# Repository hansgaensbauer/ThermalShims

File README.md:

# Thermal Shims

## Shim Demos

### Concentric Rings

This demonstration uses a 4mm ferrite plate cut to size on a waterjet. Each ring is connected to a PCB heater that is counterwound to prevent the development of magnetic fields from the heater current.

### 12x12 Array

This board demonstrates independent closed-loop control over the temperature of 144 ferrite elements. Each ferrite element has a temperature control unit cell attached on the backside of the PCB. This circuit uses two dual-MOSFETs to provide DRAM-like array access to the power setting and temperature readout for that element:

These unit cells can then be connected to form a larger array of N elements, with only sqrt(N) control circuits/ADCs required:

The `12x12 Array` folder contains simulations of the control circuits showing the sequencing required to measure the temperature or set the cell power level. All of this circuitry is included on the PCB for the 12x12 array demo.

### Hub & Spoke NdFeB Magnet Shimming

This board provides temperature control and sensing for 32 NdFeB magnets in a hub & spoke magnet array. This can be used to prevent temperature drift between the magnets during a scan, or even to account for variations in the magnetization of the individual elements. 

## Simulations
The jupyter notebook in the Simulations folder includes code for simulating different arrangements of thermal shims with different temperatures using [FEMM](https://www.femm.info/). These simulations assume an arctangent B/H curve that is parameterized by a linear relationship between the saturation magnetization and the temperature:

To run a simulation with a certain material and temperature, the code creates a custom material based on the calculated BH curve in FEMM. To sweep the temperature, the same simulation is run with different materials.

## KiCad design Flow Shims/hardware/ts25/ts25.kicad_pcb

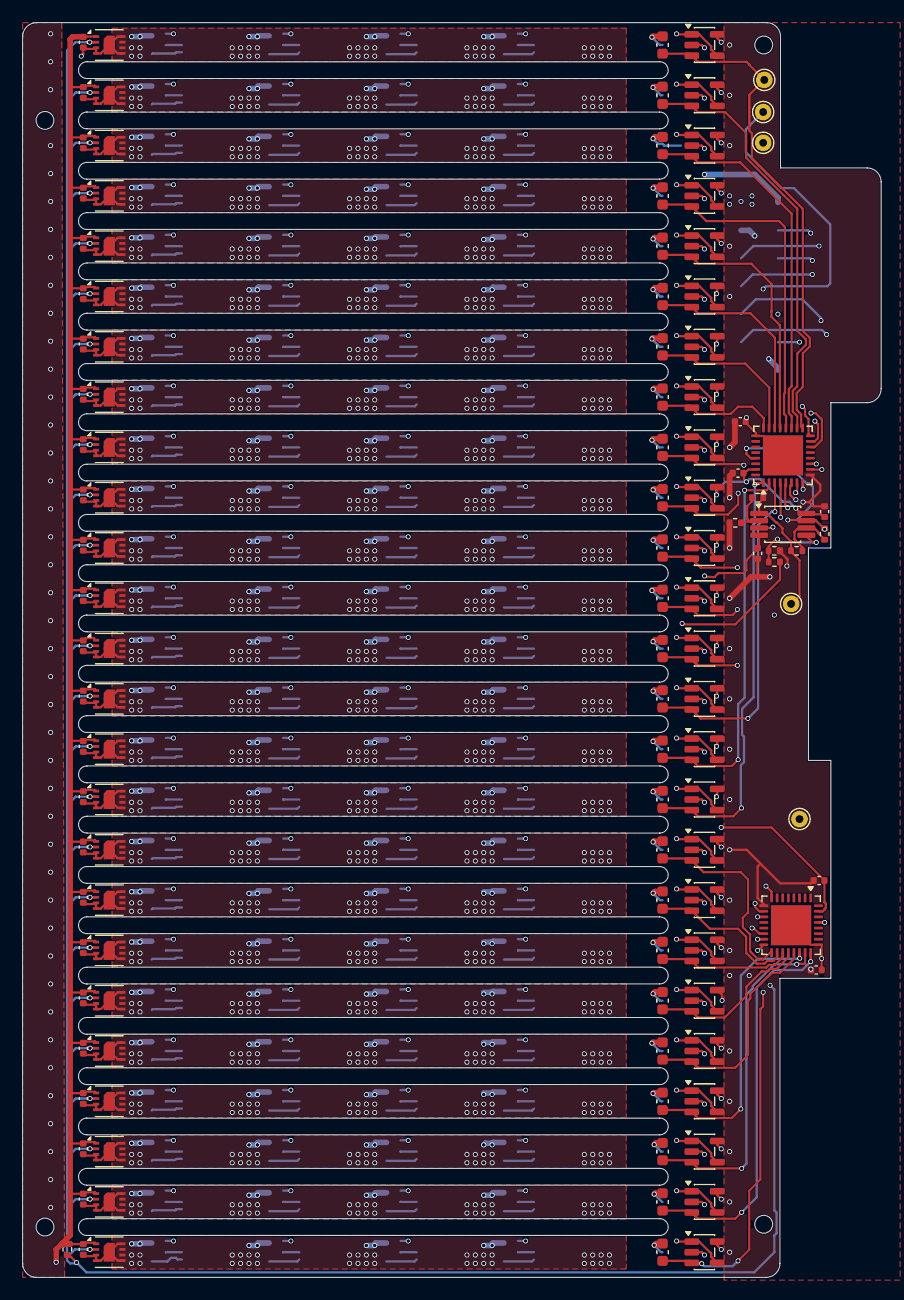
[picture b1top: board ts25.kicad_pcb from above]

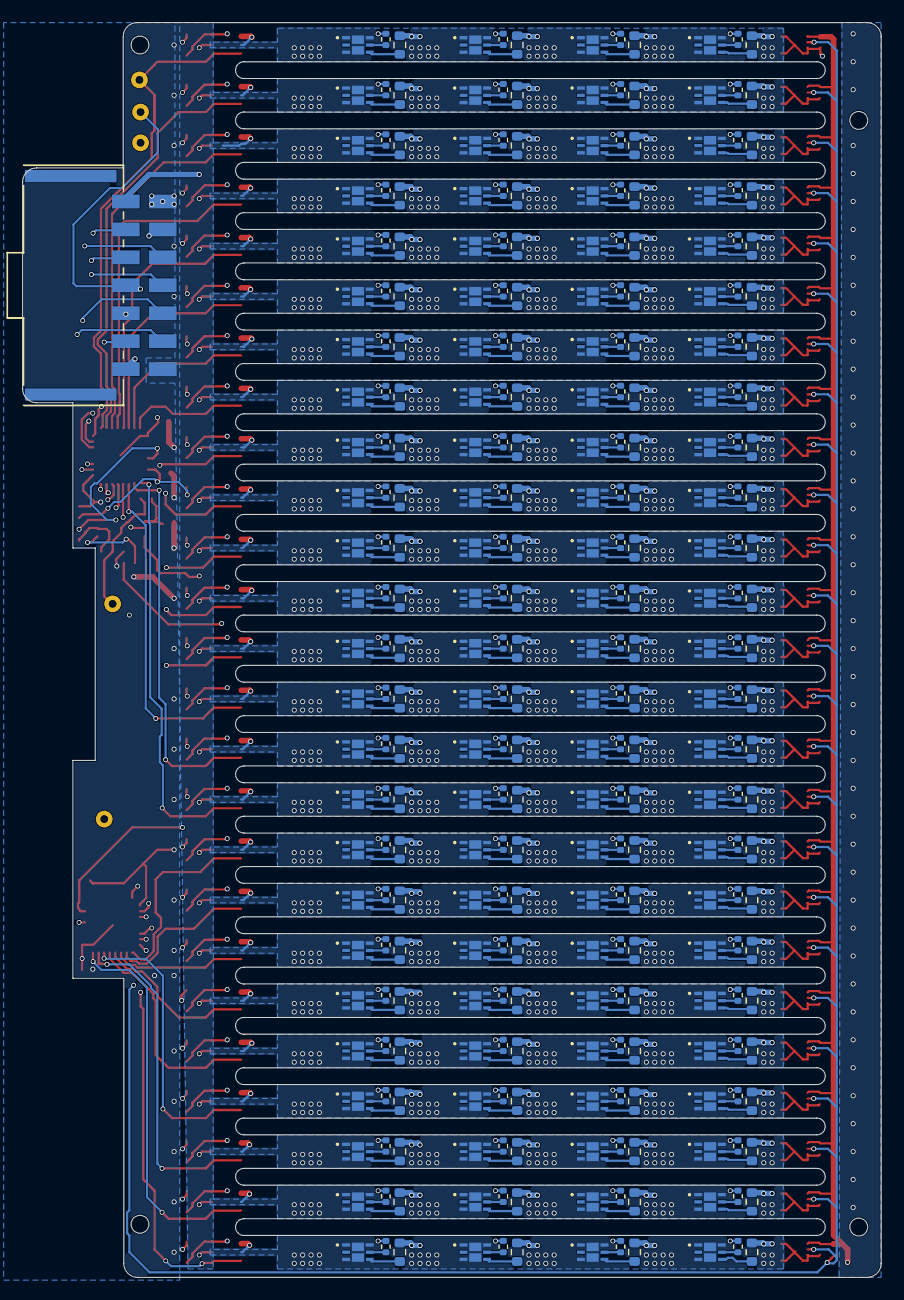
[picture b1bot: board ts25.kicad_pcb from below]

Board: 4 copper layers, 76.8 x 112.2 mm, 422 parts (301 on the bottom side), 269 nets.

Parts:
C1, C2, C3, C4, C5, C6, C7, C8, C9, C10, C11, C12, C13, C14, C15, C16, C17, C18, C19, C20, C21, C22, C23, C24, C25, C26, C27, C28, C29, C56, C57: 100n; C_0402_1005Metric
C30, C31, C32, C33, C34, C35, C36, C37, C38, C39, C40, C41, C42, C43, C44, C45, C46, C47, C48, C49, C50, C51, C52, C53, C54: 100n; C_0603_1608Metric
J2: Nano-Fit; CONN_SD-105405-001_14_MOL
R1: R_Small; R_0402_1005Metric
R2, R3, R4, R5, R6, R7: 10k; R_0402_1005Metric
R8, R9, R10, R11, R12, R13, R14, R15, R16, R17, R18, R19, R20, R21, R22, R23, R24, R25, R26, R27, R28, R29, R30, R31, R32, R59, R61, R63, R65, R67, R69, R71, R73, R75, R77, R79, R81, R83, R85, R87, R89, R91, R93, R95, R97, R99, R101, R103, R105, R107, R109, R111, R113, R115, R117, R119, R121, R123, R125, R127, R129, R131, R133, R135, R137, R139, R141, R143, R145, R147, R149, R151, R153, R155, R157, R159, R161, R163, R165, R167, R169, R171, R173, R175, R177, R179, R181, R183, R185, R187, R189, R191, R193, R195, R197, R199, R201, R203, R205, R207: 5; R_0603_1608Metric
R33, R34, R35, R36, R37, R38, R39, R40, R41, R42, R43, R44, R45, R46, R47, R48, R49, R50, R51, R52, R53, R54, R55, R56, R57, R58, R60, R62, R64, R66, R68, R70, R72, R74, R76, R78, R80, R82, R84, R86, R88, R90, R92, R94, R96, R98, R100, R102, R104, R106, R108, R110, R112, R114, R116, R118, R120, R122, R124, R126, R128, R130, R132, R134, R136, R138, R140, R142, R144, R146, R148, R150, R152, R154, R156, R158, R160, R162, R164, R166, R168, R170, R172, R174, R176, R178, R180, R182, R184, R186, R188, R190, R192, R194, R196, R198, R200, R202, R204, R206: 10; R_0402_1005Metric
TP1, TP2, TP3, TP4, TP5: TestPoint; TestPoint_THTPad_D1.5mm_Drill0.7mm
U1, U27: ADG5206; QFN-32-1EP_5x5mm_P0.5mm_EP3.6x3.6mm
U2, U3, U4, U5, U6, U7, U8, U9, U10, U11, U12, U13, U14, U15, U16, U17, U18, U19, U20, U21, U22, U23, U24, U25, U26: TMP1826NG; Sensirion_DFN-8-1EP_2.5x2.5mm_P0.5mm_EP1.1x1.7mm
U28: OPA2196xDGK; VSSOP-8_3x3mm_P0.65mm
U29, U30, U31, U32, U33, U34, U35, U36, U37, U38, U39, U40, U41, U42, U43, U44, U45, U46, U47, U48, U49, U50, U51, U52, U78, U79, U80, U81, U82, U83, U84, U85, U86, U87, U88, U89, U90, U91, U92, U93, U94, U95, U96, U97, U98, U99, U100, U101, U102, U103, U104, U105, U106, U107, U108, U109, U110, U111, U112, U113, U114, U115, U116, U117, U118, U119, U120, U121, U122, U123, U124, U125, U126, U127, U128, U129, U130, U131, U132, U133, U134, U135, U136, U137, U138, U139, U140, U141, U142, U143, U144, U145, U146, U147, U148, U149, U150, U151, U152, U153: WDFN6_2x2_ONS-M
U53, U54, U55, U56, U57, U58, U59, U60, U61, U62, U63, U64, U65, U66, U67, U68, U69, U70, U71, U72, U73, U74, U75, U76, U77: OPA196xDBV; SOT-23-5

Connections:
+3.3V: C1.2, C2.2, C3.2, C4.2, C5.2, C6.2, C7.2, C8.2, C9.2, C10.2, C11.2, C12.2, C13.2, C14.2, C15.2, C16.2, C17.2, C18.2, C19.2, C20.2, C21.2, C22.2, C23.2, C24.2, C25.2, J2.6, R1.2, U2.1 (V+), U3.1 (V+), U4.1 (V+), U5.1 (V+), U6.1 (V+), U7.1 (V+), U8.1 (V+), U9.1 (V+), U10.1 (V+), U11.1 (V+), U12.1 (V+), U13.1 (V+), U14.1 (V+), U15.1 (V+), U16.1 (V+), U17.1 (V+), U18.1 (V+), U19.1 (V+), U20.1 (V+), U21.1 (V+), U22.1 (V+), U23.1 (V+), U24.1 (V+), U25.1 (V+), U26.1 (V+)
+15V: C28.2, C29.2, C56.1, J2.8, U1.31 (VDD), U27.31 (VDD), U28.8 (V+), U53.5 (V+), U54.5 (V+), U55.5 (V+), U56.5 (V+), U57.5 (V+), U58.5 (V+), U59.5 (V+), U60.5 (V+), U61.5 (V+), U62.5 (V+), U63.5 (V+), U64.5 (V+), U65.5 (V+), U66.5 (V+), U67.5 (V+), U68.5 (V+), U69.5 (V+), U70.5 (V+), U71.5 (V+), U72.5 (V+), U73.5 (V+), U74.5 (V+), U75.5 (V+), U76.5 (V+), U77.5 (V+)
-15V: C26.2, C27.2, C57.1, J2.14, U1.25 (VSS), U1.33 (PAD), U27.25 (VSS), U27.33 (PAD), U28.4 (V-), U53.2 (V-), U54.2 (V-), U55.2 (V-), U56.2 (V-), U57.2 (V-), U58.2 (V-), U59.2 (V-), U60.2 (V-), U61.2 (V-), U62.2 (V-), U63.2 (V-), U64.2 (V-), U65.2 (V-), U66.2 (V-), U67.2 (V-), U68.2 (V-), U69.2 (V-), U70.2 (V-), U71.2 (V-), U72.2 (V-), U73.2 (V-), U74.2 (V-), U75.2 (V-), U76.2 (V-), U77.2 (V-)
/A0: J2.5, U1.15 (A0), U27.15 (A0)
/A1: J2.4, U1.14 (A1), U27.14 (A1)
/A2: J2.3, U1.11 (A2), U27.11 (A2)
/A3: J2.2, U1.10 (A3), U27.10 (A3)
/EN0: J2.12, U1.16 (EN)
/EN1: J2.13, U27.16 (EN)
/VG: R7.1, TP4.1 (1_1), U1.29 (D), U27.29 (D), U28.7
/VG1: C30.1, TP5.1 (1_1), U1.17 (S1), U53.3 (+)
/VG2: C31.1, U1.18 (S2), U54.3 (+)
/VG3: C32.1, U1.19 (S3), U55.3 (+)
/VG4: C33.1, U1.20 (S4), U56.3 (+)
/VG5: C34.1, U1.21 (S5), U57.3 (+)
/VG6: C35.1, U1.22 (S6), U58.3 (+)
/VG7: C36.1, U1.23 (S7), U59.3 (+)
/VG8: C37.1, U1.24 (S8), U60.3 (+)
/VG9: C38.1, U1.8 (S9), U61.3 (+)
/VG10: C39.1, U1.7 (S10), U62.3 (+)
/VG11: C40.1, U1.6 (S11), U63.3 (+)
/VG12: C41.1, U1.5 (S12), U64.3 (+)
/VG13: C42.1, U1.4 (S13), U65.3 (+)
/VG14: C43.1, U1.3 (S14), U66.3 (+)
/VG15: C44.1, U1.2 (S15), U67.3 (+)
/VG16: C45.1, U1.1 (S16), U68.3 (+)
/VG17: C46.1, U27.17 (S1), U69.3 (+)
/VG18: C47.1, U27.18 (S2), U70.3 (+)
/VG19: C48.1, U27.19 (S3), U71.3 (+)
/VG20: C49.1, U27.20 (S4), U72.3 (+)
/VG21: C50.1, U27.21 (S5), U73.3 (+)
/VG22: C51.1, U27.22 (S6), U74.3 (+)
/VG23: C52.1, U27.23 (S7), U75.3 (+)
/VG24: C53.1, U27.24 (S8), U76.3 (+)
/VG25: C54.1, U27.8 (S9), U77.3 (+)
/VGIN: J2.11, TP2.1 (1_1), U28.3 (+)
/VTEMP: J2.10, R1.1, U2.2 (SDQ), U3.2 (SDQ), U4.2 (SDQ), U5.2 (SDQ), U6.2 (SDQ), U7.2 (SDQ), U8.2 (SDQ), U9.2 (SDQ), U10.2 (SDQ), U11.2 (SDQ), U12.2 (SDQ), U13.2 (SDQ), U14.2 (SDQ), U15.2 (SDQ), U16.2 (SDQ), U17.2 (SDQ), U18.2 (SDQ), U19.2 (SDQ), U20.2 (SDQ), U21.2 (SDQ), U22.2 (SDQ), U23.2 (SDQ), U24.2 (SDQ), U25.2 (SDQ), U26.2 (SDQ)
GND: C1.1, C2.1, C3.1, C4.1, C5.1, C6.1, C7.1, C8.1, C9.1, C10.1, C11.1, C12.1, C13.1, C14.1, C15.1, C16.1, C17.1, C18.1, C19.1, C20.1, C21.1, C22.1, C23.1, C24.1, C25.1, C26.1, C27.1, C28.1, C29.1, C30.2, C31.2, C32.2, C33.2, C34.2, C35.2, C36.2, C37.2, C38.2, C39.2, C40.2, C41.2, C42.2, C43.2, C44.2, C45.2, C46.2, C47.2, C48.2, C49.2, C50.2, C51.2, C52.2, C53.2, C54.2, C56.2, C57.2, J2.1, R3.1, R4.1, U1.9 (GND), U2.3 (ADDR), U2.4 (GND), U2.5 (IO3), U2.6 (IO0), U2.7 (IO1), U2.8 (~ALERT), U2.9 (PAD), U3.3 (ADDR), U3.4 (GND), U3.5 (IO3), U3.6 (IO0), U3.7 (IO1), U3.8 (~ALERT), U3.9 (PAD), U4.3 (ADDR), U4.4 (GND), U4.5 (IO3), U4.6 (IO0), U4.7 (IO1), U4.8 (~ALERT), U4.9 (PAD), U5.3 (ADDR), U5.4 (GND), U5.5 (IO3), U5.6 (IO0), U5.7 (IO1), U5.8 (~ALERT), U5.9 (PAD), U6.3 (ADDR), U6.4 (GND), U6.5 (IO3), U6.6 (IO0), U6.7 (IO1), U6.8 (~ALERT), U6.9 (PAD), U7.3 (ADDR), U7.4 (GND), U7.5 (IO3), U7.6 (IO0), U7.7 (IO1), U7.8 (~ALERT), U7.9 (PAD), U8.3 (ADDR), U8.4 (GND), U8.5 (IO3), U8.6 (IO0), U8.7 (IO1), U8.8 (~ALERT), U8.9 (PAD), U9.3 (ADDR), U9.4 (GND), U9.5 (IO3), U9.6 (IO0), U9.7 (IO1), U9.8 (~ALERT), U9.9 (PAD), U10.3 (ADDR), U10.4 (GND), U10.5 (IO3), U10.6 (IO0), U10.7 (IO1), U10.8 (~ALERT), U10.9 (PAD), U11.3 (ADDR), U11.4 (GND), U11.5 (IO3), U11.6 (IO0), U11.7 (IO1), U11.8 (~ALERT), U11.9 (PAD), U12.3 (ADDR), U12.4 (GND), U12.5 (IO3), U12.6 (IO0), U12.7 (IO1), U12.8 (~ALERT), U12.9 (PAD), U13.3 (ADDR), U13.4 (GND), U13.5 (IO3), U13.6 (IO0), U13.7 (IO1), U13.8 (~ALERT), U13.9 (PAD), U14.3 (ADDR), U14.4 (GND), U14.5 (IO3), U14.6 (IO0), U14.7 (IO1), U14.8 (~ALERT), U14.9 (PAD), U15.3 (ADDR), U15.4 (GND), U15.5 (IO3), U15.6 (IO0), U15.7 (IO1), U15.8 (~ALERT), U15.9 (PAD), U16.3 (ADDR), U16.4 (GND), U16.5 (IO3), U16.6 (IO0), U16.7 (IO1), U16.8 (~ALERT), U16.9 (PAD), U17.3 (ADDR), U17.4 (GND), U17.5 (IO3), U17.6 (IO0), U17.7 (IO1), U17.8 (~ALERT), U17.9 (PAD), U18.3 (ADDR), U18.4 (GND), U18.5 (IO3), U18.6 (IO0), U18.7 (IO1), U18.8 (~ALERT), U18.9 (PAD), U19.3 (ADDR), U19.4 (GND), U19.5 (IO3), U19.6 (IO0), U19.7 (IO1), U19.8 (~ALERT), U19.9 (PAD), U20.3 (ADDR), U20.4 (GND), U20.5 (IO3), U20.6 (IO0), U20.7 (IO1), U20.8 (~ALERT), U20.9 (PAD), U21.3 (ADDR), U21.4 (GND), U21.5 (IO3), U21.6 (IO0), U21.7 (IO1), U21.8 (~ALERT), U21.9 (PAD), U22.3 (ADDR), U22.4 (GND), U22.5 (IO3), U22.6 (IO0), U22.7 (IO1), U22.8 (~ALERT), U22.9 (PAD), U23.3 (ADDR), U23.4 (GND), U23.5 (IO3), U23.6 (IO0), U23.7 (IO1), U23.8 (~ALERT), U23.9 (PAD), U24.3 (ADDR), U24.4 (GND), U24.5 (IO3), U24.6 (IO0), U24.7 (IO1), U24.8 (~ALERT), U24.9 (PAD), U25.3 (ADDR), U25.4 (GND), U25.5 (IO3), U25.6 (IO0), U25.7 (IO1), U25.8 (~ALERT), U25.9 (PAD), U26.3 (ADDR), U26.4 (GND), U26.5 (IO3), U26.6 (IO0), U26.7 (IO1), U26.8 (~ALERT), U26.9 (PAD), U27.9 (GND), U29.1 (A), U29.3 (D), U29.6 (K), U29.7 (K), U29.8 (D), U30.1 (A), U30.3 (D), U30.6 (K), U30.7 (K), U30.8 (D), U31.1 (A), U31.3 (D), U31.6 (K), U31.7 (K), U31.8 (D), U32.1 (A), U32.3 (D), U32.6 (K), U32.7 (K), U32.8 (D), U33.1 (A), U33.3 (D), U33.6 (K), U33.7 (K), U33.8 (D), U34.1 (A), U34.3 (D), U34.6 (K), U34.7 (K), U34.8 (D), U35.1 (A), U35.3 (D), U35.6 (K), U35.7 (K), U35.8 (D), U36.1 (A), U36.3 (D), U36.6 (K), U36.7 (K), U36.8 (D), U37.1 (A), U37.3 (D), U37.6 (K), U37.7 (K), U37.8 (D), U38.1 (A), U38.3 (D), U38.6 (K), U38.7 (K), U38.8 (D), U39.1 (A), U39.3 (D), U39.6 (K), U39.7 (K), U39.8 (D), U40.1 (A), U40.3 (D), U40.6 (K), U40.7 (K), U40.8 (D), U41.1 (A), U41.3 (D), U41.6 (K), U41.7 (K), U41.8 (D), U42.1 (A), U42.3 (D), U42.6 (K), U42.7 (K), U42.8 (D), U43.1 (A), U43.3 (D), U43.6 (K), U43.7 (K), U43.8 (D), U44.1 (A), U44.3 (D), U44.6 (K), U44.7 (K), U44.8 (D), U45.1 (A), U45.3 (D), U45.6 (K), U45.7 (K), U45.8 (D), U46.1 (A), U46.3 (D), U46.6 (K), U46.7 (K), U46.8 (D), U47.1 (A), U47.3 (D), U47.6 (K), U47.7 (K), U47.8 (D), U48.1 (A), U48.3 (D), U48.6 (K), U48.7 (K), U48.8 (D), U49.1 (A), U49.3 (D), U49.6 (K), U49.7 (K), U49.8 (D), U50.1 (A), U50.3 (D), U50.6 (K), U50.7 (K), U50.8 (D), U51.1 (A), U51.3 (D), U51.6 (K), U51.7 (K), U51.8 (D), U52.1 (A), U52.3 (D), U52.6 (K), U52.7 (K), U52.8 (D), U78.1 (A), U78.3 (D), U78.6 (K), U78.7 (K), U78.8 (D), U79.1 (A), U79.3 (D), U79.6 (K), U79.7 (K), U79.8 (D), U80.1 (A), U80.3 (D), U80.6 (K), U80.7 (K), U80.8 (D), U81.1 (A), U81.3 (D), U81.6 (K), U81.7 (K), U81.8 (D), U82.1 (A), U82.3 (D), U82.6 (K), U82.7 (K), U82.8 (D), U83.1 (A), U83.3 (D), U83.6 (K), U83.7 (K), U83.8 (D), U84.1 (A), U84.3 (D), U84.6 (K), U84.7 (K), U84.8 (D), U85.1 (A), U85.3 (D), U85.6 (K), U85.7 (K), U85.8 (D), U86.1 (A), U86.3 (D), U86.6 (K), U86.7 (K), U86.8 (D), U87.1 (A), U87.3 (D), U87.6 (K), U87.7 (K), U87.8 (D), U88.1 (A), U88.3 (D), U88.6 (K), U88.7 (K), U88.8 (D), U89.1 (A), U89.3 (D), U89.6 (K), U89.7 (K), U89.8 (D), U90.1 (A), U90.3 (D), U90.6 (K), U90.7 (K), U90.8 (D), U91.1 (A), U91.3 (D), U91.6 (K), U91.7 (K), U91.8 (D), U92.1 (A), U92.3 (D), U92.6 (K), U92.7 (K), U92.8 (D), U93.1 (A), U93.3 (D), U93.6 (K), U93.7 (K), U93.8 (D), U94.1 (A), U94.3 (D), U94.6 (K), U94.7 (K), U94.8 (D), U95.1 (A), U95.3 (D), U95.6 (K), U95.7 (K), U95.8 (D), U96.1 (A), U96.3 (D), U96.6 (K), U96.7 (K), U96.8 (D), U97.1 (A), U97.3 (D), U97.6 (K), U97.7 (K), U97.8 (D), U98.1 (A), U98.3 (D), U98.6 (K), U98.7 (K), U98.8 (D), U99.1 (A), U99.3 (D), U99.6 (K), U99.7 (K), U99.8 (D), U100.1 (A), U100.3 (D), U100.6 (K), U100.7 (K), U100.8 (D), U101.1 (A), U101.3 (D), U101.6 (K), U101.7 (K), U101.8 (D), U102.1 (A), U102.3 (D), U102.6 (K), U102.7 (K), U102.8 (D), U103.1 (A), U103.3 (D), U103.6 (K), U103.7 (K), U103.8 (D), U104.1 (A), U104.3 (D), U104.6 (K), U104.7 (K), U104.8 (D), U105.1 (A), U105.3 (D), U105.6 (K), U105.7 (K), U105.8 (D), U106.1 (A), U106.3 (D), U106.6 (K), U106.7 (K), U106.8 (D), U107.1 (A), U107.3 (D), U107.6 (K), U107.7 (K), U107.8 (D), U108.1 (A), U108.3 (D), U108.6 (K), U108.7 (K), U108.8 (D), U109.1 (A), U109.3 (D), U109.6 (K), U109.7 (K), U109.8 (D), U110.1 (A), U110.3 (D), U110.6 (K), U110.7 (K), U110.8 (D), U111.1 (A), U111.3 (D), U111.6 (K), U111.7 (K), U111.8 (D), U112.1 (A), U112.3 (D), U112.6 (K), U112.7 (K), U112.8 (D), U113.1 (A), U113.3 (D), U113.6 (K), U113.7 (K), U113.8 (D), U114.1 (A), U114.3 (D), U114.6 (K), U114.7 (K), U114.8 (D), U115.1 (A), U115.3 (D), U115.6 (K), U115.7 (K), U115.8 (D), U116.1 (A), U116.3 (D), U116.6 (K), U116.7 (K), U116.8 (D), U117.1 (A), U117.3 (D), U117.6 (K), U117.7 (K), U117.8 (D), U118.1 (A), U118.3 (D), U118.6 (K)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
unnamed: J2.9, TP1.1 (1_1)
unnamed: R2.2, R6.1, TP3.1 (1_1), U28.1
unnamed: R2.1, R3.2, U28.2 (-)
unnamed: R4.2, R5.1, U28.5 (+)
unnamed: R6.2, R7.2, U28.6 (-)
unnamed: R33.1, U29.5 (G)
unnamed: R8.2, U29.4 (S)
unnamed: R34.1, U30.5 (G)
unnamed: R9.2, U30.4 (S)
unnamed: R35.1, U31.5 (G)
unnamed: R10.2, U31.4 (S)
unnamed: R36.1, U32.5 (G)
unnamed: R11.2, U32.4 (S)
unnamed: R37.1, U33.5 (G)
unnamed: R12.2, U33.4 (S)
unnamed: R38.1, U34.5 (G)
unnamed: R13.2, U34.4 (S)
unnamed: R39.1, U35.5 (G)
unnamed: R14.2, U35.4 (S)
unnamed: R40.1, U36.5 (G)
unnamed: R15.2, U36.4 (S)
unnamed: R41.1, U37.5 (G)
unnamed: R16.2, U37.4 (S)
unnamed: R42.1, U38.5 (G)
unnamed: R17.2, U38.4 (S)
unnamed: R43.1, U39.5 (G)
unnamed: R18.2, U39.4 (S)
unnamed: R44.1, U40.5 (G)
unnamed: R19.2, U40.4 (S)
unnamed: R45.1, U41.5 (G)
unnamed: R20.2, U41.4 (S)
unnamed: R46.1, U42.5 (G)
unnamed: R21.2, U42.4 (S)
unnamed: R47.1, U43.5 (G)
unnamed: R22.2, U43.4 (S)
unnamed: R48.1, U44.5 (G)
unnamed: R23.2, U44.4 (S)
unnamed: R49.1, U45.5 (G)
unnamed: R24.2, U45.4 (S)
unnamed: R50.1, U46.5 (G)
unnamed: R25.2, U46.4 (S)
unnamed: R51.1, U47.5 (G)
unnamed: R26.2, U47.4 (S)
unnamed: R52.1, U48.5 (G)
unnamed: R27.2, U48.4 (S)
unnamed: R53.1, U49.5 (G)
unnamed: R28.2, U49.4 (S)
unnamed: R54.1, U50.5 (G)
unnamed: R29.2, U50.4 (S)
unnamed: R55.1, U51.5 (G)
unnamed: R30.2, U51.4 (S)
unnamed: R56.1, U52.5 (G)
unnamed: R31.2, U52.4 (S)
unnamed: R33.2, R58.2, R108.2, R158.2, U53.1, U53.4 (-)
unnamed: R34.2, R60.2, R110.2, R160.2, U54.1, U54.4 (-)
unnamed: R35.2, R62.2, R112.2, R162.2, U55.1, U55.4 (-)
unnamed: R36.2, R64.2, R114.2, R164.2, U56.1, U56.4 (-)
unnamed: R37.2, R66.2, R116.2, R166.2, U57.1, U57.4 (-)
unnamed: R38.2, R68.2, R118.2, R168.2, U58.1, U58.4 (-)
unnamed: R39.2, R70.2, R120.2, R170.2, U59.1, U59.4 (-)
unnamed: R40.2, R72.2, R122.2, R172.2, U60.1, U60.4 (-)
unnamed: R41.2, R74.2, R124.2, R174.2, U61.1, U61.4 (-)
unnamed: R42.2, R76.2, R126.2, R176.2, U62.1, U62.4 (-)
unnamed: R43.2, R78.2, R128.2, R178.2, U63.1, U63.4 (-)
unnamed: R44.2, R80.2, R130.2, R180.2, U64.1, U64.4 (-)
unnamed: R45.2, R82.2, R132.2, R182.2, U65.1, U65.4 (-)
unnamed: R46.2, R84.2, R134.2, R184.2, U66.1, U66.4 (-)
unnamed: R47.2, R86.2, R136.2, R186.2, U67.1, U67.4 (-)
unnamed: R48.2, R88.2, R138.2, R188.2, U68.1, U68.4 (-)
unnamed: R49.2, R90.2, R140.2, R190.2, U69.1, U69.4 (-)
unnamed: R50.2, R92.2, R142.2, R192.2, U70.1, U70.4 (-)
unnamed: R51.2, R94.2, R144.2, R194.2, U71.1, U71.4 (-)
unnamed: R52.2, R96.2, R146.2, R196.2, U72.1, U72.4 (-)
unnamed: R53.2, R98.2, R148.2, R198.2, U73.1, U73.4 (-)
unnamed: R54.2, R100.2, R150.2, R200.2, U74.1, U74.4 (-)
unnamed: R55.2, R102.2, R152.2, R202.2, U75.1, U75.4 (-)
unnamed: R56.2, R104.2, R154.2, R204.2, U76.1, U76.4 (-)
unnamed: R57.2, R106.2, R156.2, R206.2, U77.1, U77.4 (-)
unnamed: R57.1, U78.5 (G)
unnamed: R32.2, U78.4 (S)
unnamed: R58.1, U79.5 (G)
unnamed: R59.2, U79.4 (S)
unnamed: R60.1, U80.5 (G)
unnamed: R61.2, U80.4 (S)
unnamed: R62.1, U81.5 (G)
unnamed: R63.2, U81.4 (S)
unnamed: R64.1, U82.5 (G)
unnamed: R65.2, U82.4 (S)
unnamed: R66.1, U83.5 (G)
unnamed: R67.2, U83.4 (S)
unnamed: R68.1, U84.5 (G)
unnamed: R69.2, U84.4 (S)
unnamed: R70.1, U85.5 (G)
unnamed: R71.2, U85.4 (S)
unnamed: R72.1, U86.5 (G)
unnamed: R73.2, U86.4 (S)
unnamed: R74.1, U87.5 (G)
unnamed: R75.2, U87.4 (S)
unnamed: R76.1, U88.5 (G)
unnamed: R77.2, U88.4 (S)
unnamed: R78.1, U89.5 (G)
unnamed: R79.2, U89.4 (S)
unnamed: R80.1, U90.5 (G)
unnamed: R81.2, U90.4 (S)
unnamed: R82.1, U91.5 (G)
unnamed: R83.2, U91.4 (S)
unnamed: R84.1, U92.5 (G)
unnamed: R85.2, U92.4 (S)
unnamed: R86.1, U93.5 (G)
unnamed: R87.2, U93.4 (S)
unnamed: R88.1, U94.5 (G)
unnamed: R89.2, U94.4 (S)
unnamed: R90.1, U95.5 (G)
unnamed: R91.2, U95.4 (S)
unnamed: R92.1, U96.5 (G)
unnamed: R93.2, U96.4 (S)
unnamed: R94.1, U97.5 (G)
unnamed: R95.2, U97.4 (S)
unnamed: R96.1, U98.5 (G)
unnamed: R97.2, U98.4 (S)
unnamed: R98.1, U99.5 (G)
unnamed: R99.2, U99.4 (S)
unnamed: R100.1, U100.5 (G)
unnamed: R101.2, U100.4 (S)
unnamed: R102.1, U101.5 (G)
unnamed: R103.2, U101.4 (S)
unnamed: R104.1, U102.5 (G)
unnamed: R105.2, U102.4 (S)
unnamed: R106.1, U103.5 (G)
unnamed: R107.2, U103.4 (S)
unnamed: R108.1, U104.5 (G)
unnamed: R109.2, U104.4 (S)
unnamed: R110.1, U105.5 (G)
unnamed: R111.2, U105.4 (S)
unnamed: R112.1, U106.5 (G)
unnamed: R113.2, U106.4 (S)
unnamed: R114.1, U107.5 (G)
unnamed: R115.2, U107.4 (S)
unnamed: R116.1, U108.5 (G)
unnamed: R117.2, U108.4 (S)
unnamed: R118.1, U109.5 (G)
unnamed: R119.2, U109.4 (S)
unnamed: R120.1, U110.5 (G)
unnamed: R121.2, U110.4 (S)
unnamed: R122.1, U111.5 (G)
unnamed: R123.2, U111.4 (S)
unnamed: R124.1, U112.5 (G)
unnamed: R125.2, U112.4 (S)
unnamed: R126.1, U113.5 (G)
unnamed: R127.2, U113.4 (S)
unnamed: R128.1, U114.5 (G)
unnamed: R129.2, U114.4 (S)
unnamed: R130.1, U115.5 (G)
unnamed: R131.2, U115.4 (S)
unnamed: R132.1, U116.5 (G)
unnamed: R133.2, U116.4 (S)
unnamed: R134.1, U117.5 (G)
unnamed: R135.2, U117.4 (S)
unnamed: R136.1, U118.5 (G)
unnamed: R137.2, U118.4 (S)
unnamed: R138.1, U119.5 (G)
unnamed: R139.2, U119.4 (S)
unnamed: R140.1, U120.5 (G)
unnamed: R141.2, U120.4 (S)
unnamed: R142.1, U121.5 (G)
unnamed: R143.2, U121.4 (S)
unnamed: R144.1, U122.5 (G)
unnamed: R145.2, U122.4 (S)
unnamed: R146.1, U123.5 (G)
unnamed: R147.2, U123.4 (S)
unnamed: R148.1, U124.5 (G)
unnamed: R149.2, U124.4 (S)
unnamed: R150.1, U125.5 (G)
unnamed: R151.2, U125.4 (S)
unnamed: R152.1, U126.5 (G)
unnamed: R153.2, U126.4 (S)
unnamed: R154.1, U127.5 (G)
unnamed: R155.2, U127.4 (S)
unnamed: R156.1, U128.5 (G)
unnamed: R157.2, U128.4 (S)
unnamed: R158.1, U129.5 (G)
unnamed: R159.2, U129.4 (S)
unnamed: R160.1, U130.5 (G)
unnamed: R161.2, U130.4 (S)
unnamed: R162.1, U131.5 (G)
unnamed: R163.2, U131.4 (S)
unnamed: R164.1, U132.5 (G)
unnamed: R165.2, U132.4 (S)
unnamed: R166.1, U133.5 (G)
unnamed: R167.2, U133.4 (S)
unnamed: R168.1, U134.5 (G)
unnamed: R169.2, U134.4 (S)
unnamed: R170.1, U135.5 (G)
unnamed: R171.2, U135.4 (S)
unnamed: R172.1, U136.5 (G)
unnamed: R173.2, U136.4 (S)
unnamed: R174.1, U137.5 (G)
unnamed: R175.2, U137.4 (S)
unnamed: R176.1, U138.5 (G)
unnamed: R177.2, U138.4 (S)
unnamed: R178.1, U139.5 (G)
unnamed: R179.2, U139.4 (S)
unnamed: R180.1, U140.5 (G)
unnamed: R181.2, U140.4 (S)
unnamed: R182.1, U141.5 (G)
unnamed: R183.2, U141.4 (S)
unnamed: R184.1, U142.5 (G)
unnamed: R185.2, U142.4 (S)
unnamed: R186.1, U143.5 (G)
unnamed: R187.2, U143.4 (S)
unnamed: R188.1, U144.5 (G)
unnamed: R189.2, U144.4 (S)
unnamed: R190.1, U145.5 (G)
unnamed: R191.2, U145.4 (S)
unnamed: R192.1, U146.5 (G)
unnamed: R193.2, U146.4 (S)
unnamed: R194.1, U147.5 (G)
unnamed: R195.2, U147.4 (S)
unnamed: R196.1, U148.5 (G)
unnamed: R197.2, U148.4 (S)
unnamed: R198.1, U149.5 (G)
unnamed: R199.2, U149.4 (S)
unnamed: R200.1, U150.5 (G)
unnamed: R201.2, U150.4 (S)
unnamed: R202.1, U151.5 (G)
unnamed: R203.2, U151.4 (S)
unnamed: R204.1, U152.5 (G)
unnamed: R205.2, U152.4 (S)
unnamed: R206.1, U153.5 (G)
unnamed: R207.2, U153.4 (S)
VD: J2.7, R5.2, R8.1, R9.1, R10.1, R11.1, R12.1, R13.1, R14.1, R15.1, R16.1, R17.1, R18.1, R19.1, R20.1, R21.1, R22.1, R23.1, R24.1, R25.1, R26.1, R27.1, R28.1, R29.1, R30.1, R31.1, R32.1, R59.1, R61.1, R63.1, R65.1, R67.1, R69.1, R71.1, R73.1, R75.1, R77.1, R79.1, R81.1, R83.1, R85.1, R87.1, R89.1, R91.1, R93.1, R95.1, R97.1, R99.1, R101.1, R103.1, R105.1, R107.1, R109.1, R111.1, R113.1, R115.1, R117.1, R119.1, R121.1, R123.1, R125.1, R127.1, R129.1, R131.1, R133.1, R135.1, R137.1, R139.1, R141.1, R143.1, R145.1, R147.1, R149.1, R151.1, R153.1, R155.1, R157.1, R159.1, R161.1, R163.1, R165.1, R167.1, R169.1, R171.1, R173.1, R175.1, R177.1, R179.1, R181.1, R183.1, R185.1, R187.1, R189.1, R191.1, R193.1, R195.1, R197.1, R199.1, R201.1, R203.1, R205.1, R207.1

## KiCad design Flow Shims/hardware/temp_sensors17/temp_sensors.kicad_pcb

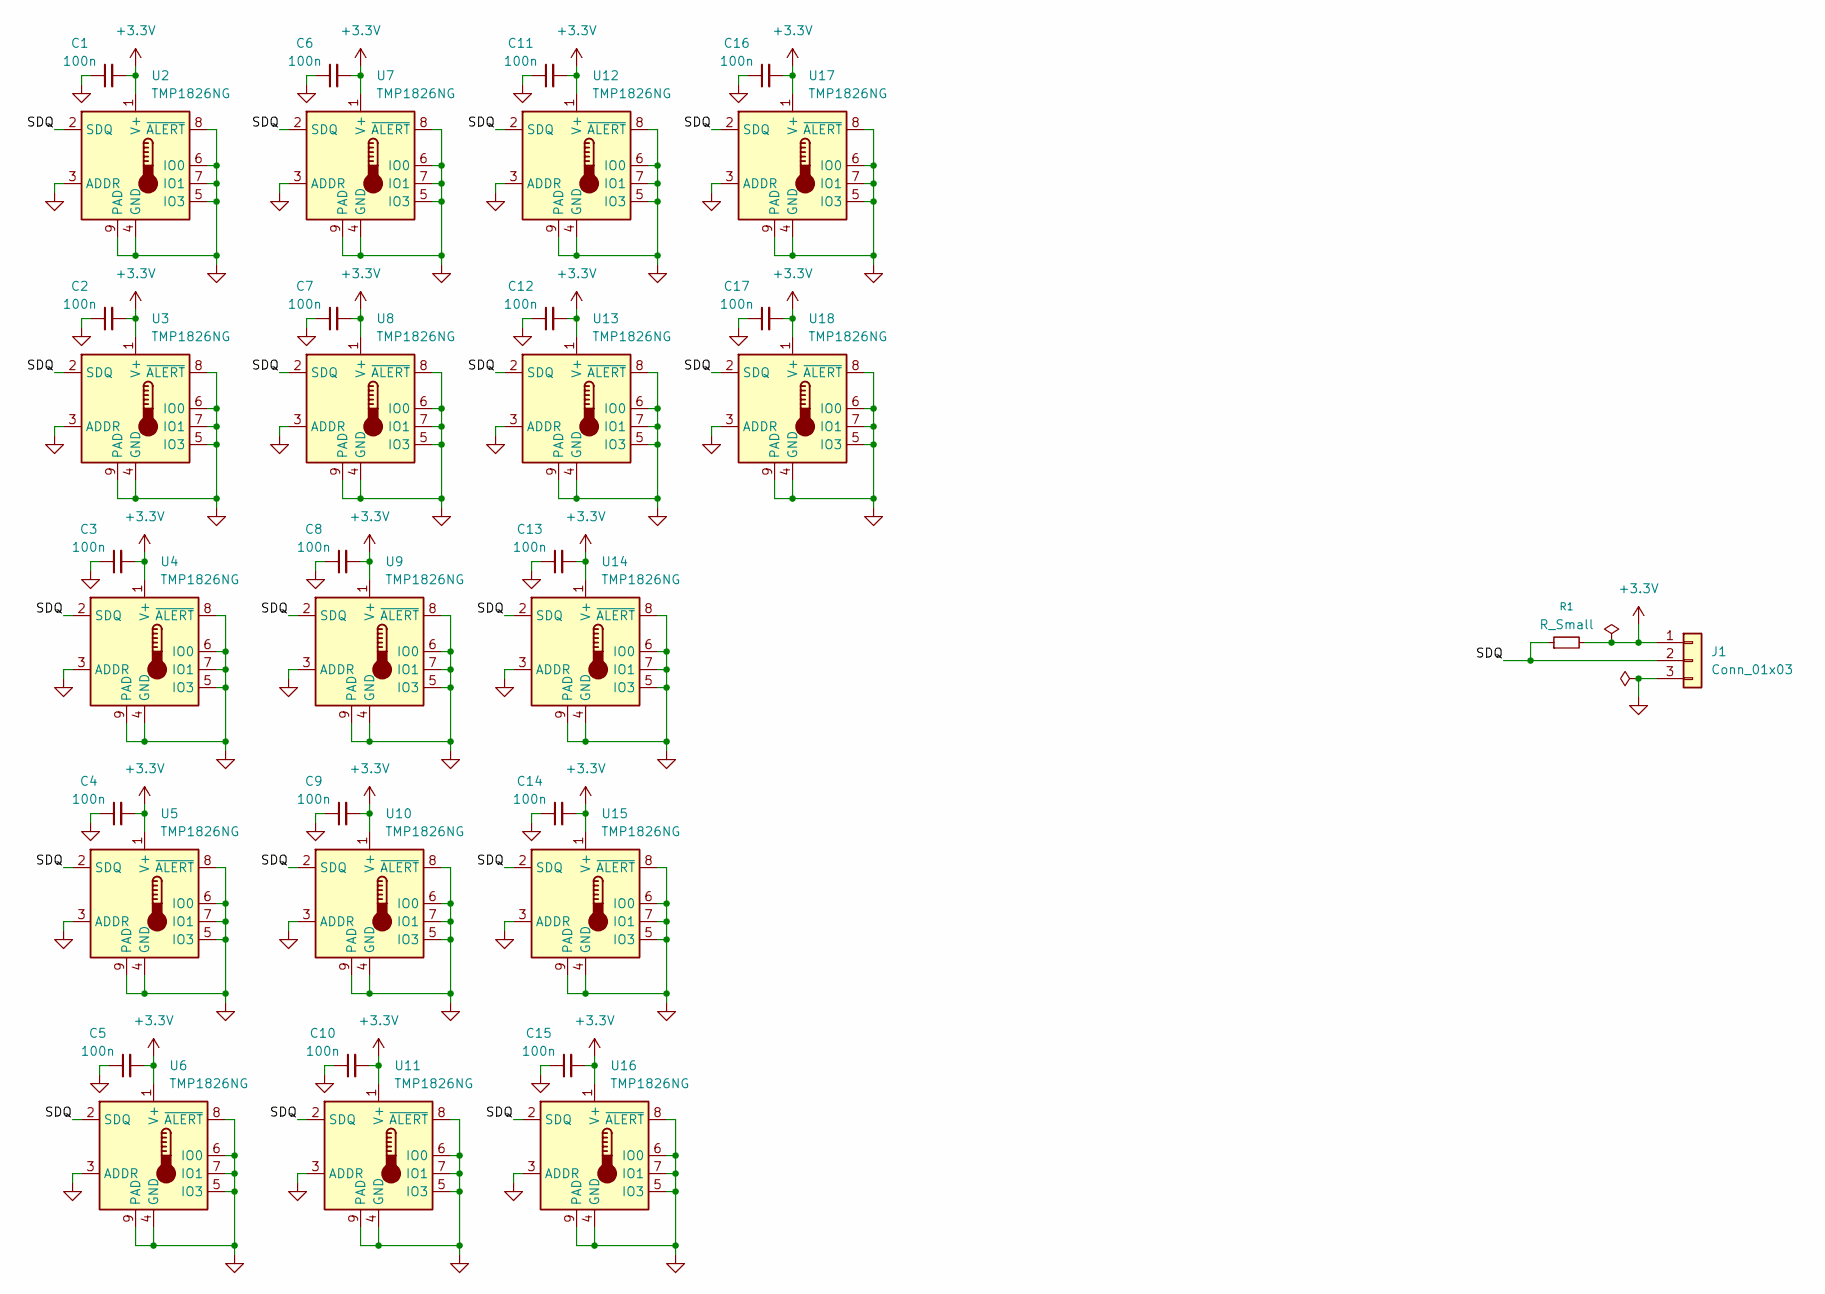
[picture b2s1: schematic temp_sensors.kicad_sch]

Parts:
C1, C2, C3, C4, C5, C6, C7, C8, C9, C10, C11, C12, C13, C14, C15, C16, C17: 100n; C_0402_1005Metric
J1: Conn_01x03; PinHeader_1x03_P1.27mm_Vertical
R1: R_Small; R_0402_1005Metric
U2, U3, U4, U5, U6, U7, U8, U9, U10, U11, U12, U13, U14, U15, U16, U17, U18: TMP1826NG; Sensirion_DFN-8-1EP_2.5x2.5mm_P0.5mm_EP1.1x1.7mm

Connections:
+3.3V: C1.2, C2.2, C3.2, C4.2, C5.2, C6.2, C7.2, C8.2, C9.2, C10.2, C11.2, C12.2, C13.2, C14.2, C15.2, C16.2, C17.2, J1.1, R1.2, U2.1 (V+), U3.1 (V+), U4.1 (V+), U5.1 (V+), U6.1 (V+), U7.1 (V+), U8.1 (V+), U9.1 (V+), U10.1 (V+), U11.1 (V+), U12.1 (V+), U13.1 (V+), U14.1 (V+), U15.1 (V+), U16.1 (V+), U17.1 (V+), U18.1 (V+)
/SDQ: J1.2, R1.1, U2.2 (SDQ), U3.2 (SDQ), U4.2 (SDQ), U5.2 (SDQ), U6.2 (SDQ), U7.2 (SDQ), U8.2 (SDQ), U9.2 (SDQ), U10.2 (SDQ), U11.2 (SDQ), U12.2 (SDQ), U13.2 (SDQ), U14.2 (SDQ), U15.2 (SDQ), U16.2 (SDQ), U17.2 (SDQ), U18.2 (SDQ)
GND: C1.1, C2.1, C3.1, C4.1, C5.1, C6.1, C7.1, C8.1, C9.1, C10.1, C11.1, C12.1, C13.1, C14.1, C15.1, C16.1, C17.1, J1.3, U2.3 (ADDR), U2.4 (GND), U2.5 (IO3), U2.6 (IO0), U2.7 (IO1), U2.8 (~ALERT), U2.9 (PAD), U3.3 (ADDR), U3.4 (GND), U3.5 (IO3), U3.6 (IO0), U3.7 (IO1), U3.8 (~ALERT), U3.9 (PAD), U4.3 (ADDR), U4.4 (GND), U4.5 (IO3), U4.6 (IO0), U4.7 (IO1), U4.8 (~ALERT), U4.9 (PAD), U5.3 (ADDR), U5.4 (GND), U5.5 (IO3), U5.6 (IO0), U5.7 (IO1), U5.8 (~ALERT), U5.9 (PAD), U6.3 (ADDR), U6.4 (GND), U6.5 (IO3), U6.6 (IO0), U6.7 (IO1), U6.8 (~ALERT), U6.9 (PAD), U7.3 (ADDR), U7.4 (GND), U7.5 (IO3), U7.6 (IO0), U7.7 (IO1), U7.8 (~ALERT), U7.9 (PAD), U8.3 (ADDR), U8.4 (GND), U8.5 (IO3), U8.6 (IO0), U8.7 (IO1), U8.8 (~ALERT), U8.9 (PAD), U9.3 (ADDR), U9.4 (GND), U9.5 (IO3), U9.6 (IO0), U9.7 (IO1), U9.8 (~ALERT), U9.9 (PAD), U10.3 (ADDR), U10.4 (GND), U10.5 (IO3), U10.6 (IO0), U10.7 (IO1), U10.8 (~ALERT), U10.9 (PAD), U11.3 (ADDR), U11.4 (GND), U11.5 (IO3), U11.6 (IO0), U11.7 (IO1), U11.8 (~ALERT), U11.9 (PAD), U12.3 (ADDR), U12.4 (GND), U12.5 (IO3), U12.6 (IO0), U12.7 (IO1), U12.8 (~ALERT), U12.9 (PAD), U13.3 (ADDR), U13.4 (GND), U13.5 (IO3), U13.6 (IO0), U13.7 (IO1), U13.8 (~ALERT), U13.9 (PAD), U14.3 (ADDR), U14.4 (GND), U14.5 (IO3), U14.6 (IO0), U14.7 (IO1), U14.8 (~ALERT), U14.9 (PAD), U15.3 (ADDR), U15.4 (GND), U15.5 (IO3), U15.6 (IO0), U15.7 (IO1), U15.8 (~ALERT), U15.9 (PAD), U16.3 (ADDR), U16.4 (GND), U16.5 (IO3), U16.6 (IO0), U16.7 (IO1), U16.8 (~ALERT), U16.9 (PAD), U17.3 (ADDR), U17.4 (GND), U17.5 (IO3), U17.6 (IO0), U17.7 (IO1), U17.8 (~ALERT), U17.9 (PAD), U18.3 (ADDR), U18.4 (GND), U18.5 (IO3), U18.6 (IO0), U18.7 (IO1), U18.8 (~ALERT), U18.9 (PAD)

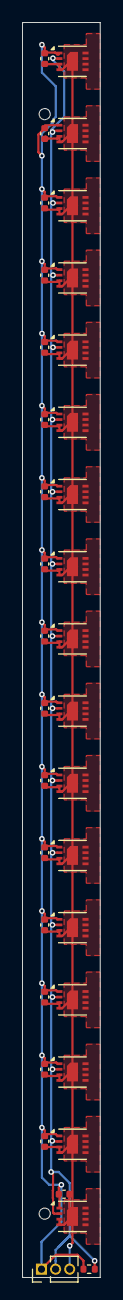
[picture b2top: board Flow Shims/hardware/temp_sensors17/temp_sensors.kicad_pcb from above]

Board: 2 copper layers, 7.0 x 113.0 mm, 36 parts (0 on the bottom side), 3 nets.

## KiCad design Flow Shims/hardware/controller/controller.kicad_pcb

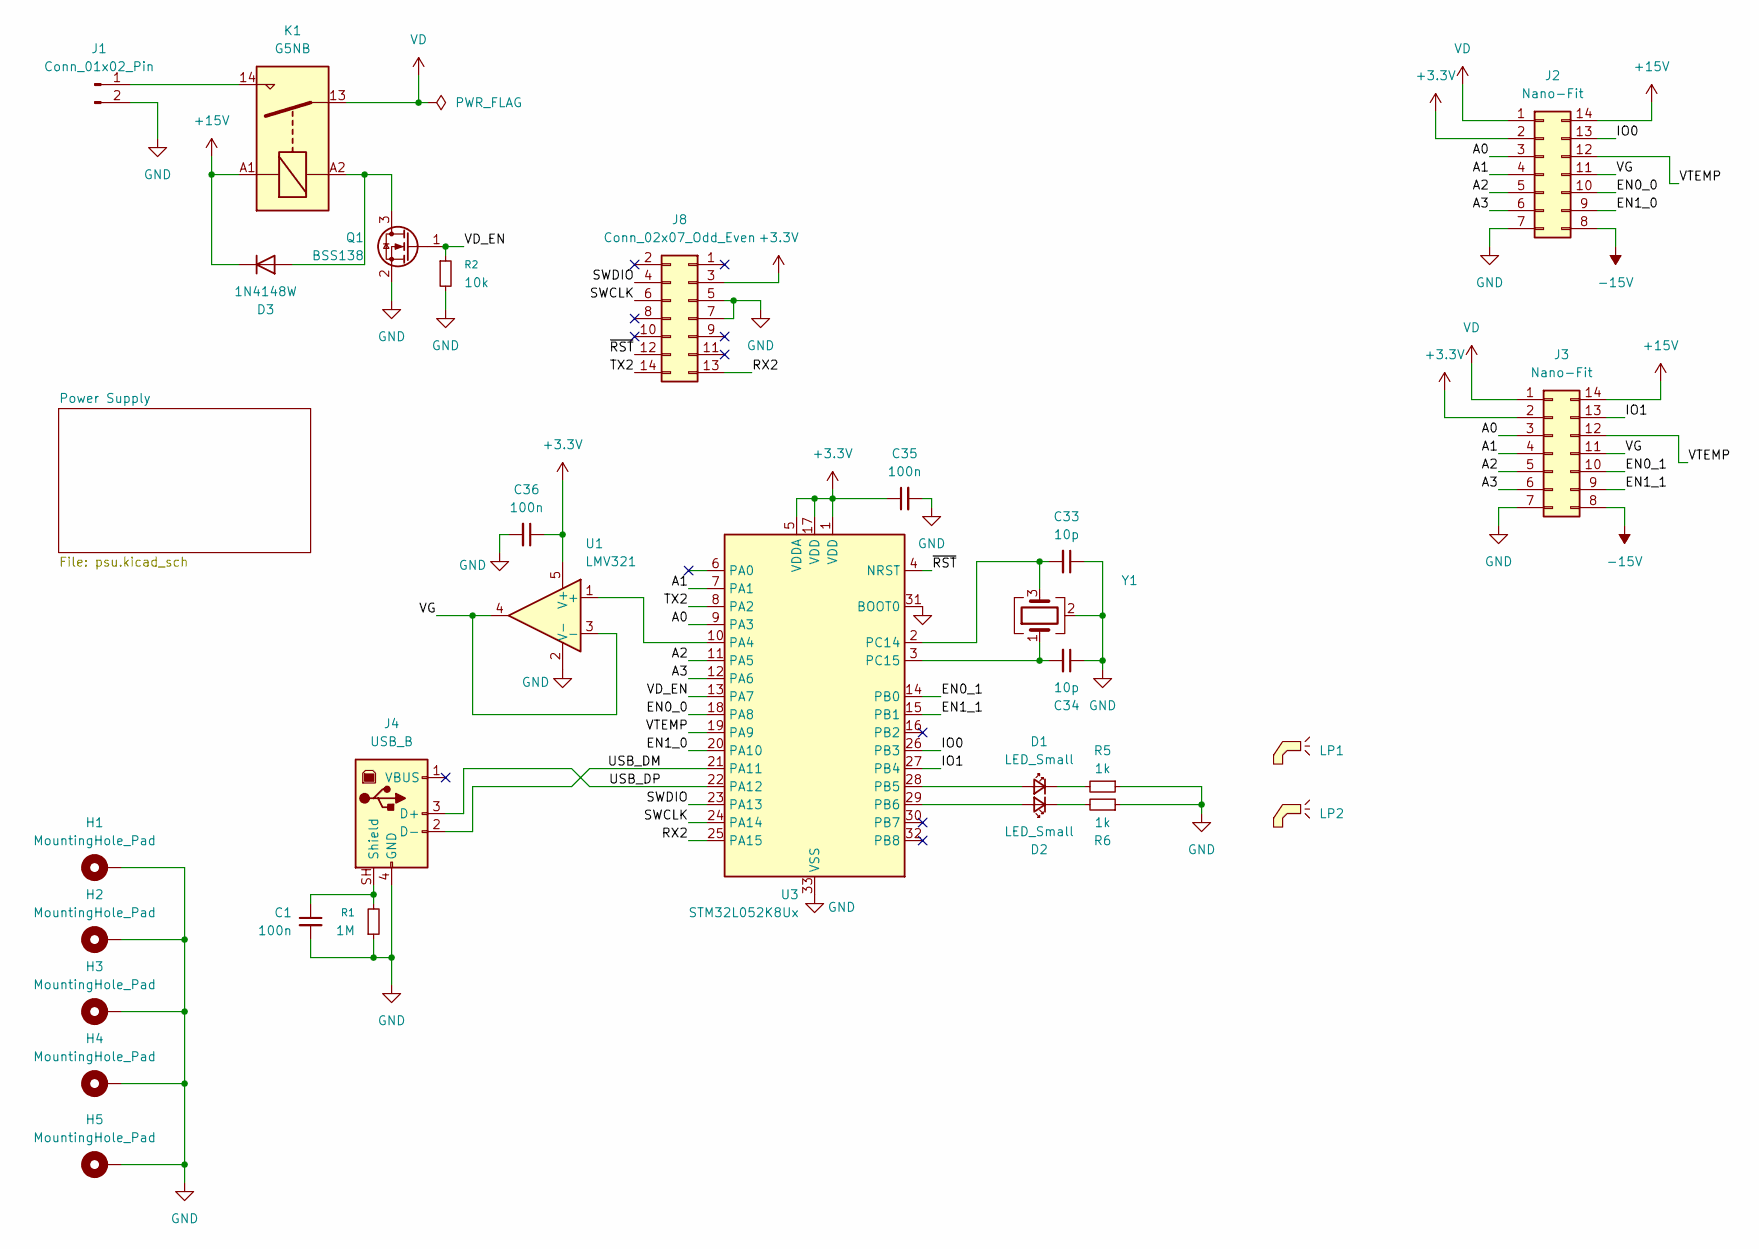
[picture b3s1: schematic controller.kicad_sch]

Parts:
C1, C35, C36: 100n; C_0603_1608Metric
C33, C34: 10p; C_0603_1608Metric
D1, D2: LED_Small; LED_0603_1608Metric
D3: 1N4148W; D_SOD-123
H1, H2, H3, H4, H5: MountingHole_Pad; MountingHole_3.2mm_M3_Pad
J1: Conn_01x02_Pin; PhoenixContact_MSTBA_2,5_2-G-5,08_1x02_P5.08mm_Horizontal
J2, J3: Nano-Fit; CONN_SD-105405-001_14_MOL
J4: USB_B; USB_B_OST_USB-B1HSxx_Horizontal
J8: Conn_02x07_Odd_Even; PinHeader_2x07_P1.27mm_Vertical_SMD
K1: G5NB; Relay_SPST_Omron_G5NB
LP1, LP2: SLP3-500-450-R
Q1: BSS138; SOT-23
R1: 1M; R_0603_1608Metric
R2: 10k
R5, R6: 1k; R_0603_1608Metric
U1: LMV321; SOT-23-5
U3: STM32L052K8Ux; QFN-32-1EP_5x5mm_P0.5mm_EP3.45x3.45mm
Y1: Crystal_GND24; Crystal_SMD_2016-4Pin_2.0x1.6mm

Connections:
+3.3V: C35.1, C36.1, J2.2, J3.2, J8.3, U1.5 (V+), U3.1 (VDD), U3.5 (VDDA), U3.17 (VDD); also elsewhere on the board
+15V: D3.1 (K), J2.14, J3.14, K1.A1; also elsewhere on the board
-15V: J2.8, J3.8; also elsewhere on the board
/A0: J2.3, J3.3, U3.9 (PA3)
/A1: J2.4, J3.4, U3.7 (PA1)
/A2: J2.5, J3.5, U3.11 (PA5)
/A3: J2.6, J3.6, U3.12 (PA6)
/EN0_0: J2.10, U3.18 (PA8)
/EN0_1: J3.10, U3.14 (PB0)
/EN1_0: J2.9, U3.20 (PA10)
/EN1_1: J3.9, U3.15 (PB1)
/IO0: J2.13, U3.26 (PB3)
/IO1: J3.13, U3.27 (PB4)
/RX2: J8.13, U3.25 (PA15)
/SWCLK: J8.6, U3.24 (PA14)
/SWDIO: J8.4, U3.23 (PA13)
/TX2: J8.14, U3.8 (PA2)
/USB_DM: J4.2 (D-), U3.21 (PA11)
/USB_DP: J4.3 (D+), U3.22 (PA12)
/VD_EN: Q1.1 (G), R2.1, U3.13 (PA7)
/VG: J2.11, J3.11, U1.3 (-), U1.4
/VTEMP: J2.12, J3.12, U3.19 (PA9)
/~RST: J8.12, U3.4 (NRST)
GND: C1.2, C33.1, C34.1, C35.2, C36.2, H1.1 (1_1), H2.1 (1_1), H3.1 (1_1), H4.1 (1_1), H5.1 (1_1), J1.2, J2.7, J3.7, J4.4 (GND), J8.5, J8.7, Q1.2 (S), R1.1, R2.2, R5.1, R6.1, U1.2 (V-), U3.31 (BOOT0), U3.33 (VSS), Y1.2 (G), Y1.4 (G); also elsewhere on the board
unnamed: D1.2 (A), U3.28 (PB5)
unnamed: D1.1 (K), R5.2
unnamed: D2.2 (A), U3.29 (PB6)
unnamed: D2.1 (K), R6.2
unnamed: D3.2 (A), K1.A2, Q1.3 (D)
unnamed: J1.1, K1.14
unnamed: C1.1, J4.SH (Shield), R1.2
unnamed: U1.1 (+), U3.10 (PA4)
unnamed: C33.2, U3.2 (PC14), Y1.3
unnamed: C34.2, U3.3 (PC15), Y1.1
VD: J2.1, J3.1, K1.13

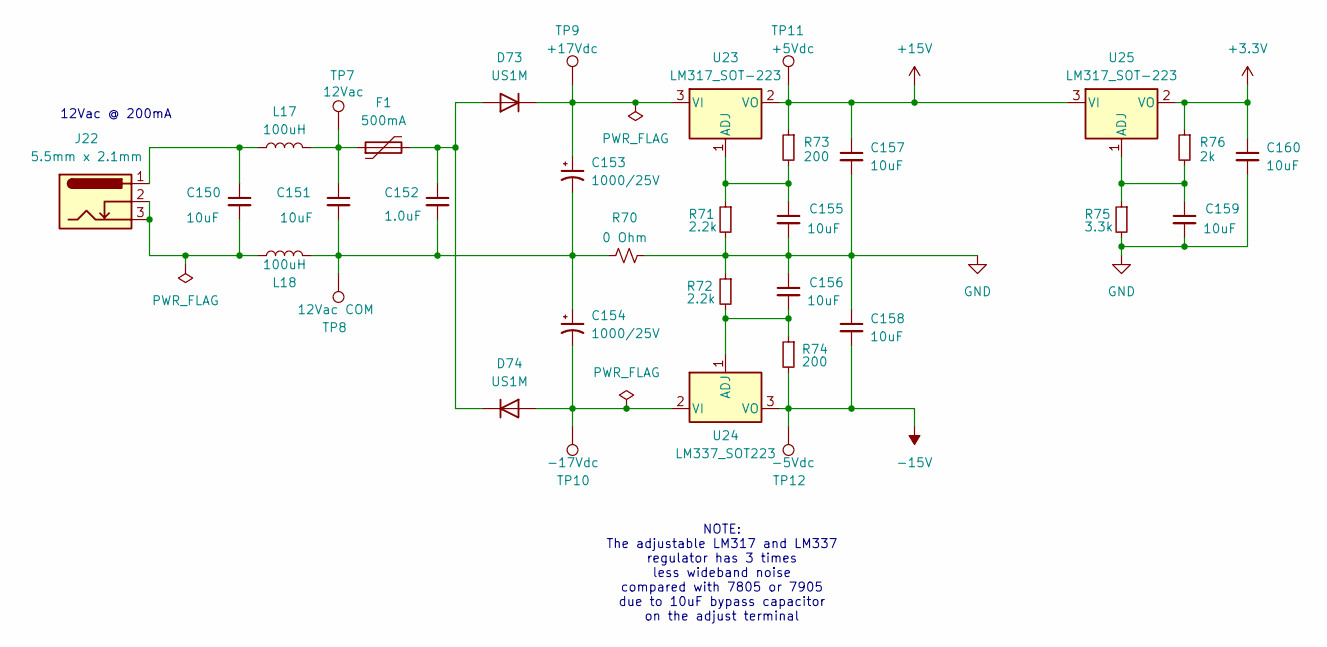
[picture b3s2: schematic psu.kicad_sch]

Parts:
C150, C151: 10uF; C_1206_3216Metric_Pad1.33x1.80mm_HandSolder
C152: 1.0uF; C_1206_3216Metric_Pad1.33x1.80mm_HandSolder
C153, C154: 1000/25V; CP_Radial_D16.0mm_P7.50mm
C155, C156, C157, C158, C159, C160: 10uF; C_1206_3216Metric
D73, D74: US1M; D_SMA
F1: 500mA; Fuse_1210_3225Metric_Pad1.42x2.65mm_HandSolder
J22: 5.5mm x 2.1mm; BarrelJack_CUI_PJ-102AH_Horizontal
L17, L18: 100uH; L_1812_4532Metric_Pad1.30x3.40mm_HandSolder
R70: 0 Ohm; R_0603_1608Metric
R71, R72: 2.2k; R_0603_1608Metric
R73, R74: 200; R_0603_1608Metric
R75: 3.3k; R_0603_1608Metric
R76: 2k; R_0603_1608Metric
TP7: 12Vac; TestPoint_Bridge_Pitch2.0mm_Drill0.7mm
TP8: 12Vac COM; TestPoint_Bridge_Pitch2.0mm_Drill0.7mm
TP9: +17Vdc; TestPoint_Bridge_Pitch2.0mm_Drill0.7mm
TP10: -17Vdc; TestPoint_Bridge_Pitch2.0mm_Drill0.7mm
TP11: +5Vdc; TestPoint_Bridge_Pitch2.0mm_Drill0.7mm
TP12: -5Vdc; TestPoint_Bridge_Pitch2.0mm_Drill0.7mm
U23, U25: LM317_SOT-223; SOT-223-3_TabPin2
U24: LM337_SOT223; SOT-223-3_TabPin2

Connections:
+3.3V: C160.1, R76.1, U25.2 (VO); also elsewhere on the board
+15V: C157.1, R73.1, TP11.1 (1_1), U23.2 (VO), U25.3 (VI); also elsewhere on the board
-15V: C158.2, R74.2, TP12.1 (1_1), U24.3 (VO); also elsewhere on the board
GND: C155.2, C156.1, C157.2, C158.1, C159.2, C160.2, R70.2, R71.2, R72.1, R75.2; also elsewhere on the board
unnamed: C150.1, J22.1, L17.1
unnamed: C150.2, J22.2, J22.3, L18.1
unnamed: C151.1, F1.1, L17.2, TP7.1 (1_1)
unnamed: C151.2, C152.2, C153.2, C154.1, L18.2, R70.1, TP8.1 (1_1)
unnamed: C152.1, D73.2 (A), D74.1 (K), F1.2
unnamed: C153.1, D73.1 (K), TP9.1 (1_1), U23.3 (VI)
unnamed: C154.2, D74.2 (A), TP10.1 (1_1), U24.2 (VI)
unnamed: C155.1, R71.1, R73.2, U23.1 (ADJ)
unnamed: C156.2, R72.2, R74.1, U24.1 (ADJ)
unnamed: C159.1, R75.1, R76.2, U25.1 (ADJ)

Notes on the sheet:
12Vac @ 200mA
NOTE: The adjustable LM317 and LM337 regulator has 3 times less wideband noise compared with 7805 or 7905 due to 10uF bypass capacitor on the adjust terminal

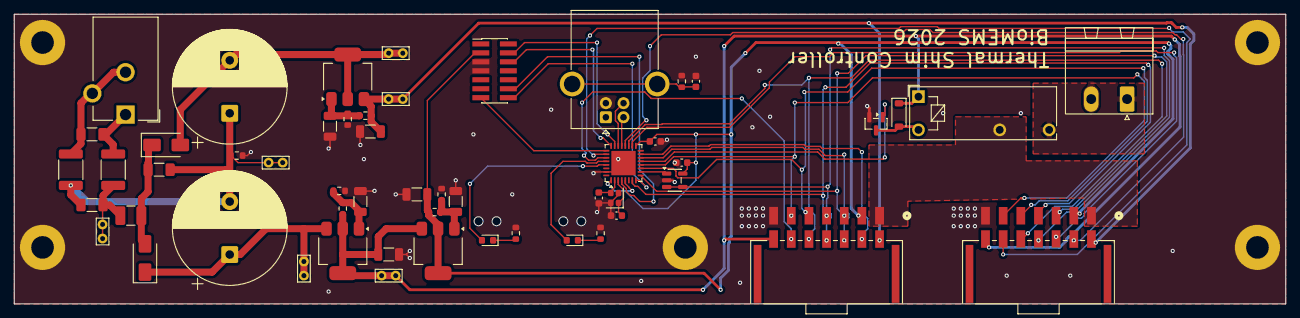
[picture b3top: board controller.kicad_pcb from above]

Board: 2 copper layers, 180.0 x 41.0 mm, 61 parts (0 on the bottom side), 45 nets.
